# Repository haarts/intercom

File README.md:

# Intercom boerderij

A home intercom built from Waveshare ESP32-P4-WIFI6-POE-ETH wall boxes. There are two routes:

- **Mumble:** the boxes run a Mumble client. There is one Mumble server for the house,
  Mumble channels route audio to rooms, and Home Assistant is integrated.
- **lanicom** (`lanicom/`): serverless. Boxes find each other on the LAN and talk
  directly, with encrypted unicast. No Mumble server, and Home Assistant is optional (it can join as a
  peer), so friends can build it too. See [lanicom/README.md](lanicom/README.md) and the
  plan with its design review in [lanicom/PLAN.md](lanicom/PLAN.md).

| Path | What |
| --- | --- |
| `lanicom/` | Serverless intercom: protocol spec, C core, ESPHome component, Python CLI, HA integration |
| `esp32-mumble/` | [dchote/esp32-mumble](https://github.com/dchote/esp32-mumble) (git subtree) with ESP32-P4 support and audio fixes. Board config: `esp32-mumble/esphome/waveshare-esp32-p4-poe.yaml` |
| `esphome/p4-bringup.yaml` | Minimal bring-up config for the board (Ethernet, codec, mic level) |
| `server/mumble/` | Docker Compose file for the Mumble server (Murmur) |
| `tools/voicetest/` | End-to-end voice test: play speech near the board, record it from Mumble, score it with Whisper |
| `PROJECT_NOTES.md` | Decisions, measurements and open items |

## Build and flash

```sh
python3 -m venv .venv && .venv/bin/pip install esphome==2026.7.1
cd esp32-mumble/esphome
../../.venv/bin/esphome run waveshare-esp32-p4-poe.yaml   # first flash over USB-C, later OTA
```

The Mumble server address is filled in automatically with Home Assistant's IP when
the device is adopted, or set it under the device's "1. Server" setting.

## Voice test

```sh
tools/voicetest/run.sh local ptt tools/voicetest/berend-nl-pad.wav nl
```

Plays the clip on this machine's default audio output, records what the board sends
to the Mumble server, and prints Whisper's transcript and word error rate. See the
comments in `run.sh` for the options.

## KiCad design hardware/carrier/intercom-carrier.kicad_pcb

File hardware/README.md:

# Intercom hardware

About ten wall boxes, each with a Waveshare ESP32-P4-ETH (sku ESP32-P4-POE-ETH, PoE module on top; no WiFi), a 40 × 40 mm speaker, four
illuminated push buttons (M19, Φ22 bezel, 3–6 V LED ring) and a 180 × 90 × 3 mm brass front
plate. The box sits on the in-wall box the UTP comes out of, with its back against the wall.

| Path | What | Status |
|---|---|---|
| `plate/front-plate-arches.dxf` | Front plate for the laser cutter | Holes corrected (below). Grille pattern still to check with the cutter. |
| `plate/front-plate-arches.scad` | The same plate for the enclosure model, generated by `plate/dxf2scad.py` | Regenerate after changing the DXF |
| `enclosure/intercom.scad` | Parametric OpenSCAD model of the 3D-printed prototype: shell, wall plate, mic tube | Carrier + ESP32-P4-ETH version, not printed yet |
| `carrier/` | KiCad project for the button/LED carrier board | Rev B in KiCad (adds the off switch J8): ERC clean, DRC 0 errors / 0 unconnected. `carrier/export/` still holds rev A, which is what was ordered. |

## GPIO map (P4-ETH header P1, Pico-style numbering)

Pin 1 is at the USB-C end of the left row, seen from the top with USB-C pointing up; pins 21–40 run back
up the right row, from the RJ45 end. Source: Waveshare's [ESP32-P4-ETH](https://docs.waveshare.com/ESP32-P4-ETH) pinout.

| Use | GPIO | P1 pin | Carrier socket |
|---|---|---|---|
| Button 1 (PTT) | GPIO23 | 31 | J7.11 |
| Button 2 | GPIO22 | 32 | J7.12 |
| Button 3 | GPIO21 | 34 | J7.14 |
| Button 4 | GPIO20 | 35 | J7.15 |
| LED ring 1 | GPIO5 | 11 | J1.11 |
| LED ring 2 | GPIO32 | 26 | J7.6 |
| LED ring 3 | GPIO4 | 12 | J1.12 |
| LED ring 4 | GPIO33 | 25 | J7.5 |
| Spare | GPIO2, GPIO3 | 15, 14 | J1.15, J1.14 → J6 |
| Off switch (`EN` = `3V3_EN`) | | 37 | J7.17 → J8 (rev B; a bodge on rev A, see below) |
| +5 V (VSYS) | | 39 | J7.19 |
| GND | | 3, 8, 13, 18, 23, 28, 33, 38 | |

## Carrier board (`carrier/`)

90 × 48 mm, two layers, through-hole only so it can be hand-soldered.

**The P4:**
- **Mounting:** it plugs in from above into two 1×20 female sockets (J1 = P1 pins 1–20, J7 = pins 21–40), 17.78 mm apart.
- **Orientation:** the silkscreen marks the RJ45 end and the USB-C end.
- **Under the P4:** only traces, so the P4's bottom-side parts are clear.
- **PoE module:** it stays on top of the P4 as usual; nothing on the carrier is near it.

**Per button** (four channels along the bottom edge, BTN1–BTN4 from left to right). The buttons are numbered in the order their GPIOs leave the header, so the four button lines run side by side without crossing:
- **Connector:** a JST-XH 4-pin. Pin 1 = LED+ (+5 V), 2 = LED−, 3 = switch, 4 = GND.
- **Switch input:** 1 kΩ in series to the GPIO, with 100 nF to GND. The pull-up is the ESP32's own; a pressed button reads low.
- **LED ring:**
  - switched low-side by a BC547, with a 1 kΩ base resistor and a 10 kΩ base pull-down that keeps it off during boot;
  - a series resistor (R13–R16) is fitted with 0 Ω (a wire link). A ring draws about 10 mA at 5 V
    (measured on a lab supply), so the rings have their own resistor and need no other.

**Also on the board:**
- 10 µF on 5 V (C5).
- J6, a 1×4 header for the spares: GPIO2, GPIO3, GND, GND. It is at the USB-C end, so don't use it while a USB cable is plugged in.
- J8 (rev B), a JST-XH 2-pin for the off switch: 1 = `3V3_EN` (P1 pin 37), 2 = GND, with C6 (100 nF) across it.
  It is in the bottom-right corner, in line with the button JSTs; J5 moved 1 mm to the left to make room.
- GND pours on both layers.
- Four M3 holes (H1–H4).

ESPHome: buttons `INPUT_PULLUP`, `inverted: true`; LEDs as `ledc` outputs (dimming, pulsing).

### Off switch

Rev B has it on J8 (above). The notes below apply to both revisions; the wiring is the rev A bodge.

A toggle switch between J7.17 (P1 pin 37) and J7.18 (pin 38, GND) turns the box off. Closed = off.
Both socket pins are free on rev A and sit next to each other, so it is two wires on the carrier and nothing on the P4.

From Waveshare's [schematic](https://files.waveshare.com/wiki/ESP32-P4-ETH/ESP32-P4-ETH-datasheet.pdf):
- **What pin 37 is:** `EN` on the header is `3V3_EN`, the enable of the MP1658 buck (U1) that makes `ESP_3V3` from 5 V.
  It is pulled up to 5 V with 10 kΩ (R21). Pulling it low removes 3.3 V from the P4, so the switch is a real power-off,
  not a reset or sleep, and firmware can't override it.
- **Pin 30 is a different pin:** `RUN` is `ESP_EN` (the RESET button). Holding it low keeps the chip in reset with everything still powered.
- **What stays powered while off:**
  - the PoE module;
  - the analog 3.3 V LDO (U8, always enabled) for the codec and mic;
  - the power LED.
- **What goes dark by itself:**
  - the speaker amp (NS4150B, CTRL = GPIO53 with a 10 kΩ pull-down);
  - the LED rings (base pull-downs).
- **In the enclosure:** a round snap-in rocker in a Ø15 cut-out in the bottom face, below J7.17/J7.18
  (`SWITCH_*` in `enclosure/intercom.scad`). Closed = off, so an I/O-marked rocker reads backwards.
- **Wiring:** keep the wires inside the box and twisted. A 100 nF cap across the switch is cheap insurance against noise on EN.
- **Switching back on** is a cold boot. Partners see the box as offline after 30 s, because no `bye` is sent.
- **Factory reset still works:** ESPHome counts power-on resets, so flicking the switch 5 times within 10 s
  does a factory reset, like 5 power cycles. That is intended: the switch is a handy reset gesture.
- **To check on the first board:**
  - with the switch off, `ESP_3V3` (pin 36) should read ~0 V. If it floats at 1–2 V, something is back-powering the P4 through its IO pins;
  - measure the power draw while off.

## Front plate

`plate/front-plate-arches.dxf` is a copy of `intercom-grill-arches.dxf` (2026-09-30) with two fixes:

- **Button holes:** Ø16 → **Ø19.4**, for the M19 switches.
- **Mounting holes:** Ø3.0 → **Ø3.3**, for M3.

The countersink note (layer `INFO_CSK`, Ø6) is unchanged.

Still open:
- the grille's minimum slot and web width, to agree with the laser cutter;
- the switches' thread length and nut size;
- each bezel's top edge touches the bottom of the grille (y = 25 mm). Check that this looks right.

## Enclosure prototype (3D print)

```
enclosure/render.sh        # needs an OpenSCAD development snapshot (2025 or later): `openscad-nightly`,
                           # `openscad`, or OPENSCAD=/path/to/OpenSCAD.AppImage
```

The model is one file, `enclosure/intercom.scad`. Every dimension a test print may change is a
parameter at its top. Open it in OpenSCAD to look around: `part` selects what is shown
(`assembly`, `shell`, `wall_plate`, `mic_tube`, `section`).

It is designed in front-view coordinates (X right, Y up, Z into the wall), the way the plate
drawing and KiCad's top view read. Every output is mirrored once into the right-handed frame
that slicers use; without that, the print would be a mirror image of the box.

`render.sh` writes to `enclosure/out/`:
- `shell`, `wall_plate` and `mic_tube`, each as `.stl` and `.3mf` (the plate is brass, so it's never in them);
- preview PNGs: front, back, iso, inside, inside_iso and a section through the carrier;
- a collision check between the shell, the plate, the electronics, the speaker, the buttons
  and the mic tube, with the electronics, speaker and buttons as blocks. It fails if any two
  of them overlap (faces that merely touch are fine);
- how much of the mic tube's bore is covered by brass where it meets the plate (should be 0 %).

The plate in the model is the real one: OpenSCAD can't read the DXF's R12 polylines, so
`plate/dxf2scad.py` converts it (`python3 dxf2scad.py front-plate-arches.dxf > front-plate-arches.scad`).

**Shell, 185.4 × 95.4 × 52 mm:**
- **Plate:** sits in a rebate, flush with the front, and is screwed to four corner bosses with M3 heat-set inserts.
- **Inside, from the left:**
  - the speaker in a closed chamber, which improves the low end; a ledge holds it against the plate;
  - the cable opening, right next to the P4's RJ45 jack;
  - the carrier on four 5 mm standoffs (M3 inserts) on the back wall, above the buttons, components towards the plate.
- **The stack, from the back wall:**
  - carrier (component side at 42.4 mm behind the front);
  - 8.5 mm sockets;
  - the ESP32-P4-ETH (component side at 32.3 mm);
  - the RJ45 and the PoE module, which stick out about 13 mm towards the plate.

  That leaves about 16 mm free behind the plate.
- **Buttons:** the JSTs are on the carrier's bottom edge, a short cable away from them.
- **Bottom:** vent slots under the carrier. Warm air leaves through the grille.
- **USB-C:** it points at the right side wall with only 9 mm to spare. Flash the P4 before you mount it; after that, update it over the network (OTA).

**Wall plate, 174 × 85 × 3 mm:**
- **Mounting:** it screws onto the in-wall box.
  - Slots fit 60 mm screw spacing, horizontal or vertical, around `WALLBOX_CENTER` (behind the cable opening by default).
  - The shell's back has recesses for the screw heads.
- **Fixing the shell:** hang the shell on the two top hooks (above the carrier) and slide it 5 mm down. Two M3 screws from below go into the wall plate's tabs.

**Print settings:** PETG (or ASA near a heat source), 0.2 mm layers, 4 perimeters around the inserts.
Print the shell with its back on the bed; the rebate and bosses need no supports.

**Hardware per box:**
- 4× M3 heat-set inserts + M3×8 countersunk screws for the plate;
- 4× M3 inserts + M3×6 screws for the carrier;
- 2× M3 inserts + M3×16 screws to fix the shell to the wall plate;
- 2 screws for the wall box (usually supplied with it).

### To verify with the first print
- **Mic:** it is on the P4, next to the USB-C, 29 mm behind the plate (`MIC_XY` in the script), and will sound muffled without help.
  It is top-port (a hole in its lid, near the end towards the USB-C), so it hears towards the plate.
  - `mic_tube.stl` runs from the plate to 3.6 mm in front of the mic, clear of the USB-C. Glue its flange behind the plate and close the last gap with a foam ring.
  - It starts behind a grille opening (`MIC_GRILLE_XY`, the bore fully open) and slants about 7° to the mic.
  - Its 3 mm bore is centred on the lid's hole, whose position is estimated (~0.8 mm from the mic's
    USB-C end). Check it against the board before gluing; `MIC_XY` moves it.
- **PoE module:** modelled as a 32 × 26 × 13 mm block. Check the real height and overhang.
- **Cable:** the RJ45 plug and the cable's bend between the jack and the cable opening. A slim patch cable helps.
- **Speaker chamber:** the wires leave through a 4 × 3 mm notch where the chamber's right wall meets the back wall.
  Seal it with hot glue after fitting, check the chamber is airtight, and add foam between the speaker and the plate.
- **Button depth:** 46 mm inside depth assumes a 33 mm body plus its plug. Measure the real buttons.
- **Button cables:** the JSTs are labelled BTN1–BTN4 from left to right; cut each cable to its button.

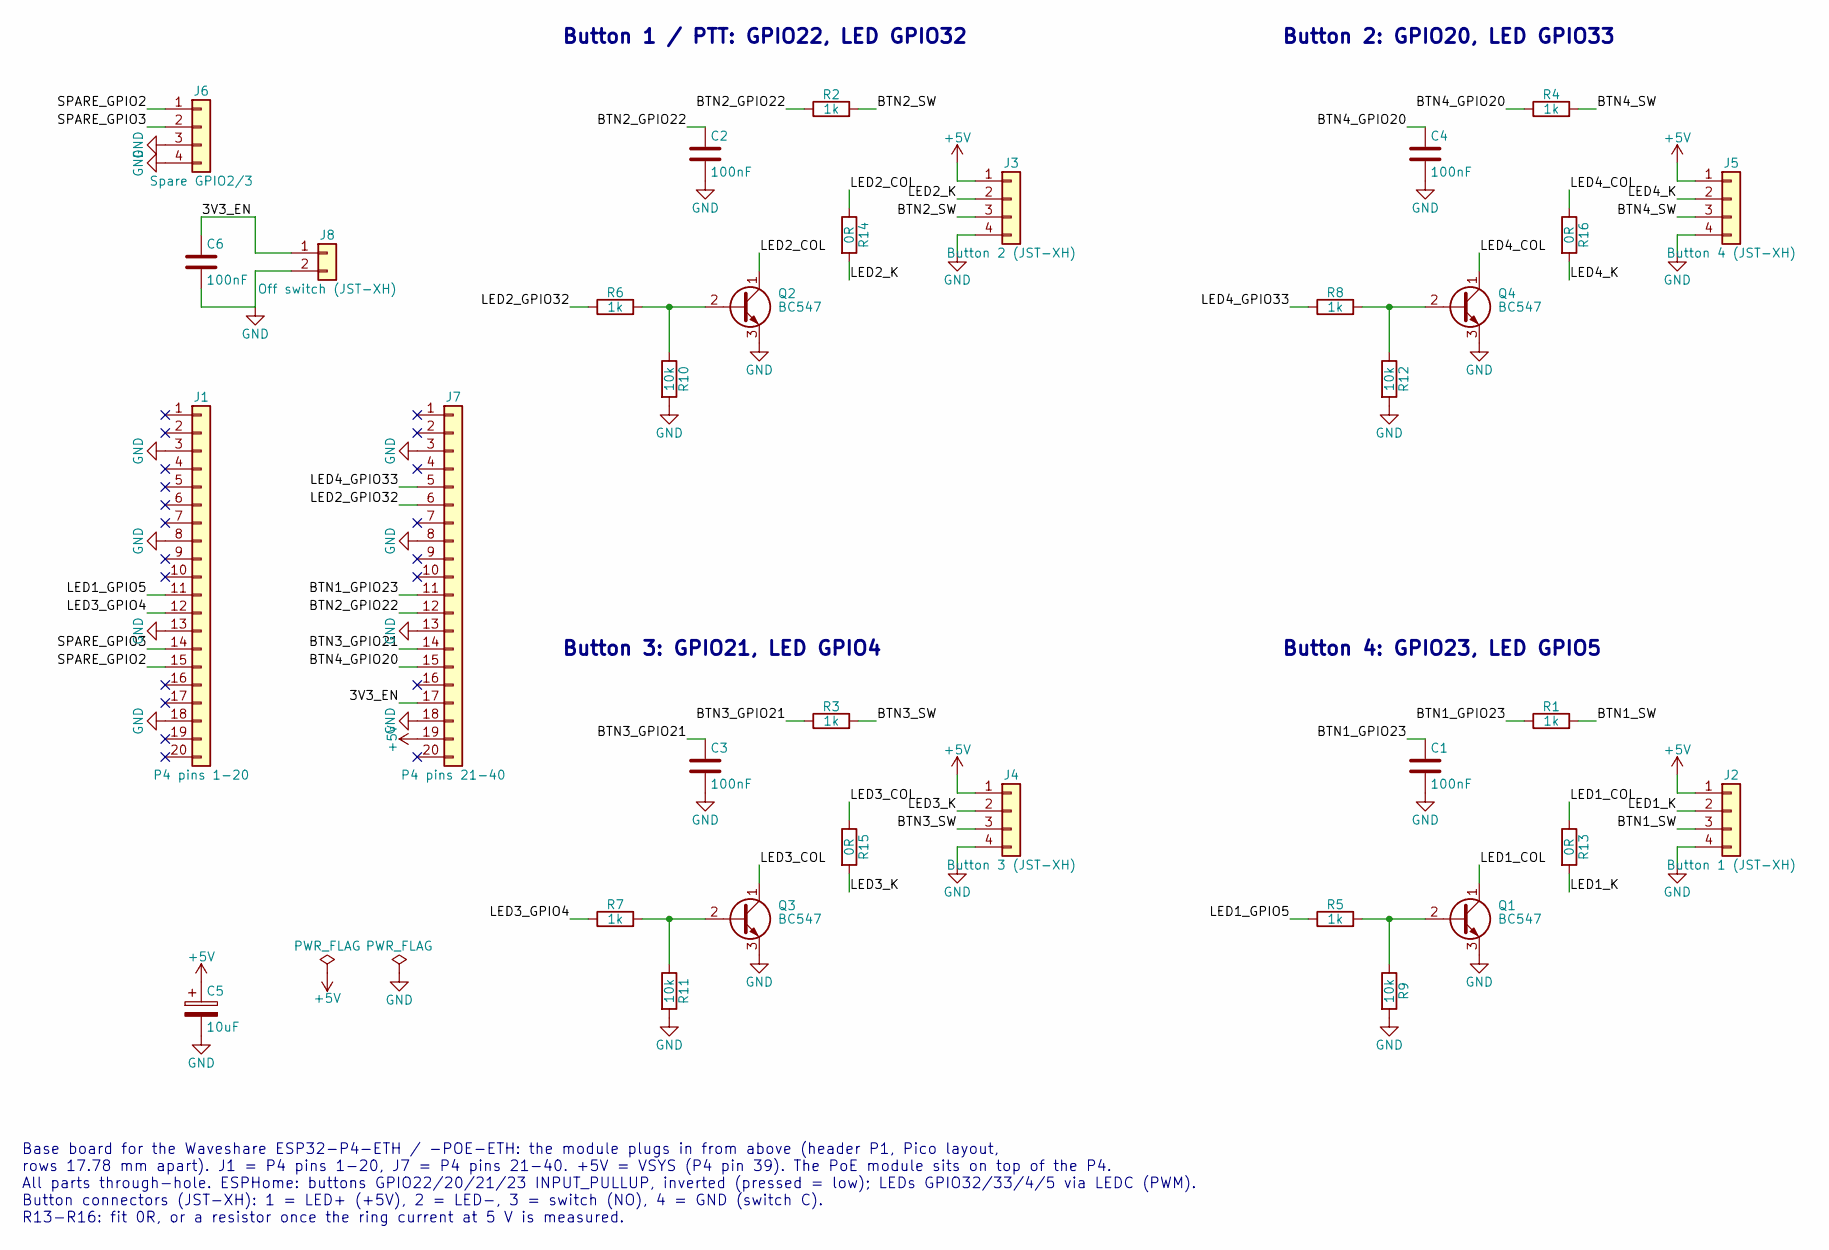
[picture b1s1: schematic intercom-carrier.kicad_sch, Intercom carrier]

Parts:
C1, C2, C3, C4, C6: 100nF; C_Disc_D3.0mm_W1.6mm_P2.50mm
C5: 10uF; CP_Radial_D5.0mm_P2.00mm
J1: P4 pins 1-20; PinSocket_1x20_P2.54mm_Vertical
J2: Button 1 (JST-XH); JST_XH_B4B-XH-A_1x04_P2.50mm_Vertical
J3: Button 2 (JST-XH); JST_XH_B4B-XH-A_1x04_P2.50mm_Vertical
J4: Button 3 (JST-XH); JST_XH_B4B-XH-A_1x04_P2.50mm_Vertical
J5: Button 4 (JST-XH); JST_XH_B4B-XH-A_1x04_P2.50mm_Vertical
J6: Spare GPIO2/3; PinHeader_1x04_P2.54mm_Vertical
J7: P4 pins 21-40; PinSocket_1x20_P2.54mm_Vertical
J8: Off switch (JST-XH); JST_XH_B2B-XH-A_1x02_P2.50mm_Vertical
Q1, Q2, Q3, Q4: BC547; TO-92_Inline
R1, R2, R3, R4, R5, R6, R7, R8: 1k; R_Axial_DIN0207_L6.3mm_D2.5mm_P7.62mm_Horizontal
R9, R10, R11, R12: 10k; R_Axial_DIN0207_L6.3mm_D2.5mm_P7.62mm_Horizontal
R13, R14, R15, R16: 0R; R_Axial_DIN0207_L6.3mm_D2.5mm_P7.62mm_Horizontal

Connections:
+5V: C5.1, J2.1, J3.1, J4.1, J5.1, J7.19
/3V3_EN: C6.1, J7.17, J8.1
/BTN1_GPIO23: C1.1, J7.11, R1.1
/BTN1_SW: J2.3, R1.2
/BTN2_GPIO22: C2.1, J7.12, R2.1
/BTN2_SW: J3.3, R2.2
/BTN3_GPIO21: C3.1, J7.14, R3.1
/BTN3_SW: J4.3, R3.2
/BTN4_GPIO20: C4.1, J7.15, R4.1
/BTN4_SW: J5.3, R4.2
/LED1_COL: Q1.1 (C), R13.1
/LED1_GPIO5: J1.11, R5.1
/LED1_K: J2.2, R13.2
/LED2_COL: Q2.1 (C), R14.1
/LED2_GPIO32: J7.6, R6.1
/LED2_K: J3.2, R14.2
/LED3_COL: Q3.1 (C), R15.1
/LED3_GPIO4: J1.12, R7.1
/LED3_K: J4.2, R15.2
/LED4_COL: Q4.1 (C), R16.1
/LED4_GPIO33: J7.5, R8.1
/LED4_K: J5.2, R16.2
/SPARE_GPIO2: J1.15, J6.1
/SPARE_GPIO3: J1.14, J6.2
GND: C1.2, C2.2, C3.2, C4.2, C5.2, C6.2, J1.3, J1.8, J1.13, J1.18, J2.4, J3.4, J4.4, J5.4, J6.3, J6.4, J7.3, J7.8, J7.13, J7.18, J8.2, Q1.3 (E), Q2.3 (E), Q3.3 (E), Q4.3 (E), R9.2, R10.2, R11.2, R12.2
unnamed: Q1.2 (B), R5.2, R9.1
unnamed: Q2.2 (B), R6.2, R10.1
unnamed: Q3.2 (B), R7.2, R11.1
unnamed: Q4.2 (B), R8.2, R12.1

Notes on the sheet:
Button 1 / PTT: GPIO22, LED GPIO32
Button 3: GPIO21, LED GPIO4
Button 2: GPIO20, LED GPIO33
Button 4: GPIO23, LED GPIO5
Base board for the Waveshare ESP32-P4-ETH / -POE-ETH: the module plugs in from above (header P1, Pico layout, rows 17.78 mm apart). J1 = P4 pins 1-20, J7 = P4 pins 21-40. +5V = VSYS (P4 pin 39). The PoE module sits on top of the P4. All parts through-hole. ESPHome: buttons GPIO22/20/21/23 INPUT_PUL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

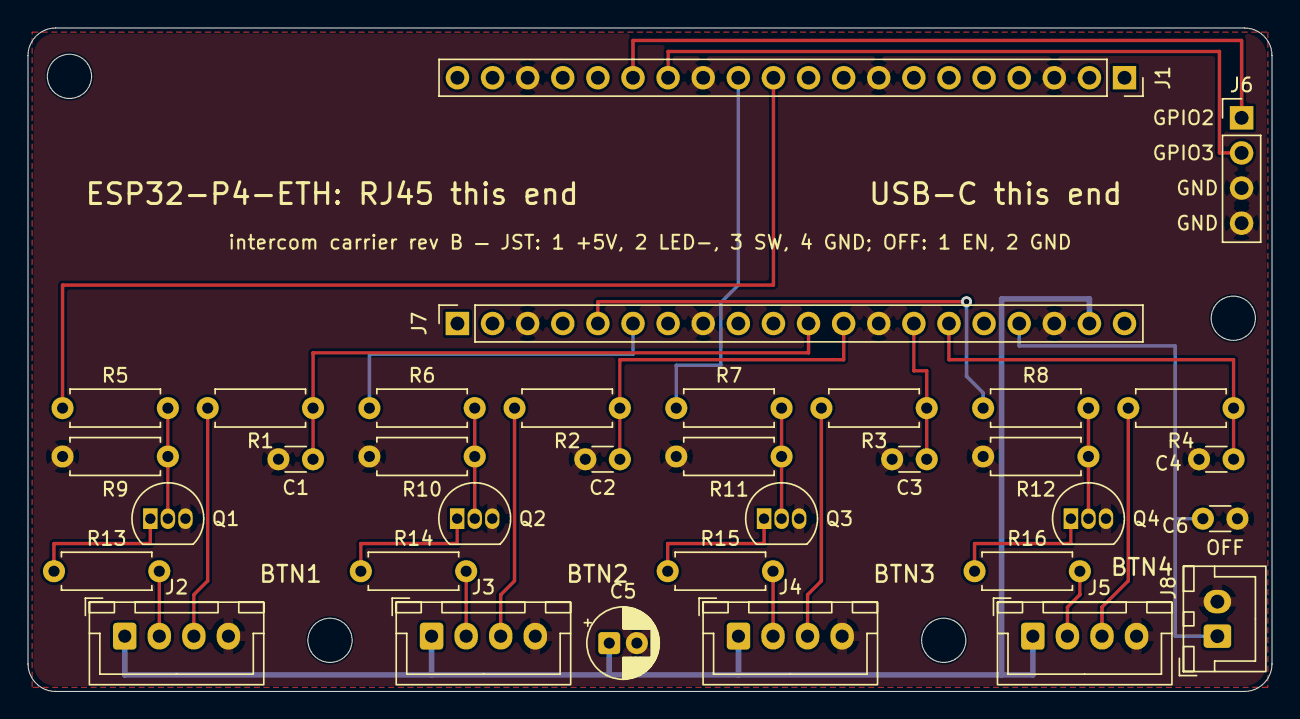
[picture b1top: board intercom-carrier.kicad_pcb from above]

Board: 2 copper layers, 90.0 x 48.0 mm, 38 parts (0 on the bottom side), 29 nets.

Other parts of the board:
H1, H2, H3, H4: MountingHole_3.2mm_M3

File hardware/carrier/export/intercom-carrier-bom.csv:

"Refs","Value","Footprint","Qty","DNP"
"C1","100nF","Capacitor_THT:C_Disc_D3.0mm_W1.6mm_P2.50mm","1",""
"C2","100nF","Capacitor_THT:C_Disc_D3.0mm_W1.6mm_P2.50mm","1",""
"C3","100nF","Capacitor_THT:C_Disc_D3.0mm_W1.6mm_P2.50mm","1",""
"C4","100nF","Capacitor_THT:C_Disc_D3.0mm_W1.6mm_P2.50mm","1",""
"C5","10uF","Capacitor_THT:CP_Radial_D5.0mm_P2.00mm","1",""
"J1","P4 pins 1-20","Connector_PinSocket_2.54mm:PinSocket_1x20_P2.54mm_Vertical","1",""
"J2","Button 1 (JST-XH)","Connector_JST:JST_XH_B4B-XH-A_1x04_P2.50mm_Vertical","1",""
"J3","Button 2 (JST-XH)","Connector_JST:JST_XH_B4B-XH-A_1x04_P2.50mm_Vertical","1",""
"J4","Button 3 (JST-XH)","Connector_JST:JST_XH_B4B-XH-A_1x04_P2.50mm_Vertical","1",""
"J5","Button 4 (JST-XH)","Connector_JST:JST_XH_B4B-XH-A_1x04_P2.50mm_Vertical","1",""
"J6","Spare GPIO2/3","Connector_PinHeader_2.54mm:PinHeader_1x04_P2.54mm_Vertical","1",""
"J7","P4 pins 21-40","Connector_PinSocket_2.54mm:PinSocket_1x20_P2.54mm_Vertical","1",""
"Q1","BC547","Package_TO_SOT_THT:TO-92_Inline","1",""
"Q2","BC547","Package_TO_SOT_THT:TO-92_Inline","1",""
"Q3","BC547","Package_TO_SOT_THT:TO-92_Inline","1",""
"Q4","BC547","Package_TO_SOT_THT:TO-92_Inline","1",""
"R1","1k","Resistor_THT:R_Axial_DIN0207_L6.3mm_D2.5mm_P7.62mm_Horizontal","1",""
"R2","1k","Resistor_THT:R_Axial_DIN0207_L6.3mm_D2.5mm_P7.62mm_Horizontal","1",""
"R3","1k","Resistor_THT:R_Axial_DIN0207_L6.3mm_D2.5mm_P7.62mm_Horizontal","1",""
"R4","1k","Resistor_THT:R_Axial_DIN0207_L6.3mm_D2.5mm_P7.62mm_Horizontal","1",""
"R5","1k","Resistor_THT:R_Axial_DIN0207_L6.3mm_D2.5mm_P7.62mm_Horizontal","1",""
"R6","1k","Resistor_THT:R_Axial_DIN0207_L6.3mm_D2.5mm_P7.62mm_Horizontal","1",""
"R7","1k","Resistor_THT:R_Axial_DIN0207_L6.3mm_D2.5mm_P7.62mm_Horizontal","1",""
"R8","1k","Resistor_THT:R_Axial_DIN0207_L6.3mm_D2.5mm_P7.62mm_Horizontal","1",""
"R9","10k","Resistor_THT:R_Axial_DIN0207_L6.3mm_D2.5mm_P7.62mm_Horizontal","1",""
"R10","10k","Resistor_THT:R_Axial_DIN0207_L6.3mm_D2.5mm_P7.62mm_Horizontal","1",""
"R11","10k","Resistor_THT:R_Axial_DIN0207_L6.3mm_D2.5mm_P7.62mm_Horizontal","1",""
"R12","10k","Resistor_THT:R_Axial_DIN0207_L6.3mm_D2.5mm_P7.62mm_Horizontal","1",""
"R13","0R","Resistor_THT:R_Axial_DIN0207_L6.3mm_D2.5mm_P7.62mm_Horizontal","1",""
"R14","0R","Resistor_THT:R_Axial_DIN0207_L6.3mm_D2.5mm_P7.62mm_Horizontal","1",""
"R15","0R","Resistor_THT:R_Axial_DIN0207_L6.3mm_D2.5mm_P7.62mm_Horizontal","1",""
"R16","0R","Resistor_THT:R_Axial_DIN0207_L6.3mm_D2.5mm_P7.62mm_Horizontal","1",""
